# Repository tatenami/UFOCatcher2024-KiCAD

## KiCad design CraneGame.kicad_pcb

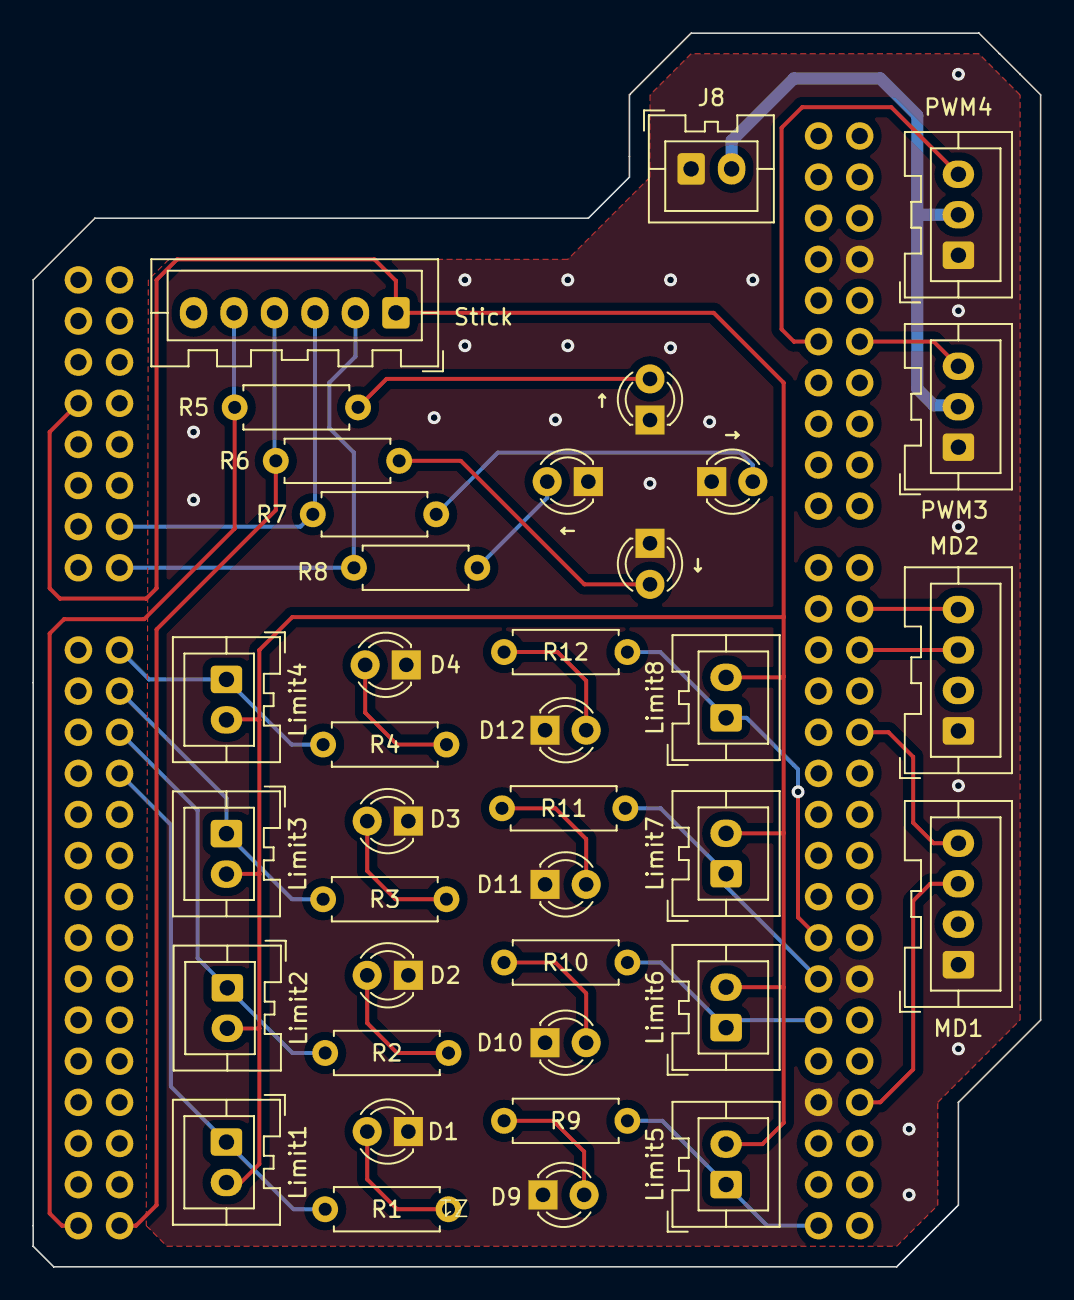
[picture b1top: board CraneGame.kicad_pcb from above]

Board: 2 copper layers, 62.2 x 76.2 mm, 39 parts (0 on the bottom side), 33 nets.

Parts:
D1, D2, D3, D4, D9, D10, D11, D12: LED; LED_D3.0mm
J8: Conn_01x02; JST_XA_B02B-XASK-1_1x02_P2.50mm_Vertical
Limit1, Limit2, Limit3, Limit4, Limit5, Limit6, Limit7, Limit8: Conn_01x02_Socket; JST_XA_B02B-XASK-1_1x02_P2.50mm_Vertical
MD1, MD2: Conn_01x04; JST_XA_B04B-XASK-1_1x04_P2.50mm_Vertical
PWM3, PWM4: Conn_01x03; JST_XA_B03B-XASK-1_1x03_P2.50mm_Vertical
R1, R2, R3, R4, R5, R6, R7, R8, R9, R10, R11, R12: R; R_Axial_DIN0207_L6.3mm_D2.5mm_P7.62mm_Horizontal
Stick: Conn_01x06_Socket; JST_XA_B06B-XASK-1_1x06_P2.50mm_Vertical
Z1: NucleoF767-ZioConnector
←: LED; LED_D3.0mm
↑: LED; LED_D3.0mm
→: LED; LED_D3.0mm
↓: LED; LED_D3.0mm

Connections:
GND: D1.1 (K), D2.1 (K), D3.1 (K), D4.1 (K), D9.1 (K), D10.1 (K), D11.1 (K), D12.1 (K), J8.1, MD1.1, MD2.1, PWM3.1, PWM4.1, Z1.37 (GND), Z1.70 (GND), Z1.77 (GND), Z1.94 (GND), ←.1 (K), ↑.1 (K), →.1 (K), ↓.1 (K)
Input←: R8.1, Stick.2, Z1.31 (PG3)
Input↑: R5.2, Stick.5, Z1.23 (PG0)
Input→: R7.1, Stick.3, Z1.30 (PG2)
Input↓: R6.2, Stick.4, Z1.46 (PG1)
Limit1: Limit1.1, R1.2, Z1.35 (PD4)
Limit2: Limit2.1, R2.2, Z1.34 (PD5)
Limit3: Limit3.1, R3.1, Z1.33 (PD6)
Limit4: Limit4.1, R4.1, Z1.32 (PD7)
Limit5: Limit5.1, R9.2, Z1.73 (PE0)
Limit6: Limit6.1, R10.2, Z1.68 (PD11)
Limit7: Limit7.1, R11.1, Z1.67 (PD12)
Limit8: Limit8.1, R12.1, Z1.66 (PD13)
unnamed: D1.2 (A), R1.1
unnamed: D2.2 (A), R2.1
unnamed: D3.2 (A), R3.2
unnamed: D4.2 (A), R4.2
unnamed: R5.1, ↑.2 (A)
unnamed: R6.1, ↓.2 (A)
unnamed: R7.2, →.2 (A)
unnamed: R8.2, ←.2 (A)
unnamed: D9.2 (A), R9.1
unnamed: D10.2 (A), R10.1
unnamed: D11.2 (A), R11.2
unnamed: D12.2 (A), R12.2
PWM1: MD2.4, Z1.85 (PE9)
PWM2: MD2.3, Z1.86 (PE11)
PWM3: MD1.4, Z1.88 (PE13)
PWM4: MD1.3, Z1.97 (PE14)
PWM5: PWM3.3, Z1.79 (PA6)
PWM6: PWM4.3, Z1.52 (PC7)
Servo_Power: J8.2, PWM3.2, PWM4.2
Switch_PWR: Limit1.2, Limit2.2, Limit3.2, Limit4.2, Limit5.2, Limit6.2, Limit7.2, Limit8.2, Stick.1, Z1.4 (3V3)
